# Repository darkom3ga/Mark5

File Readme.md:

<br />
<div align="center">
  
  <h3 align="center">Kratos Mark 5 </h3>
</div>

<details>
  <summary>Table of Contents</summary>
  <ol>
    <a href="#automating-the-running-of-the-rover">Automating the Working of the Rover</a>
    <a href="#bashrc-setup">Bashrc Setup</a>
  </ol>
</details>

## Getting Started

This repo is for easy of run of the Kratos rover and make it more organised .

## Automating the Working of the Rover

1. Install the required packages
    ```sh
    sudo apt install terminator xdotool sshpass
    ```
2. Git clone the repository and place the file named "kratos" in the ~/ directory ( home directory )</br>OR</br>Just Run the code 
    ```sh
    wget -P ~/ https://raw.githubusercontent.com/darkom3ga/Mark5/refs/heads/main/kratos
    ```

3. Run the command 
    ```sh
    chmod +x ~/kratos
    ```

4. Now run the kratos file from any terminal. 
    ```sh
    ~/kratos
    ```
    Type the Option and then hit Enter . Dont interefere / click while the automation is going one . It usually takes few second if the connections are ok .

## Bashrc Setup 

### In BaseStation

  ```sh
    export ROS_MASTER_URI=http://192.168.1.12:11311
    export ROS_IP=192.168.1.11
  ```

<p align="right">(<a href="#readme-top">back to top</a>)</p>

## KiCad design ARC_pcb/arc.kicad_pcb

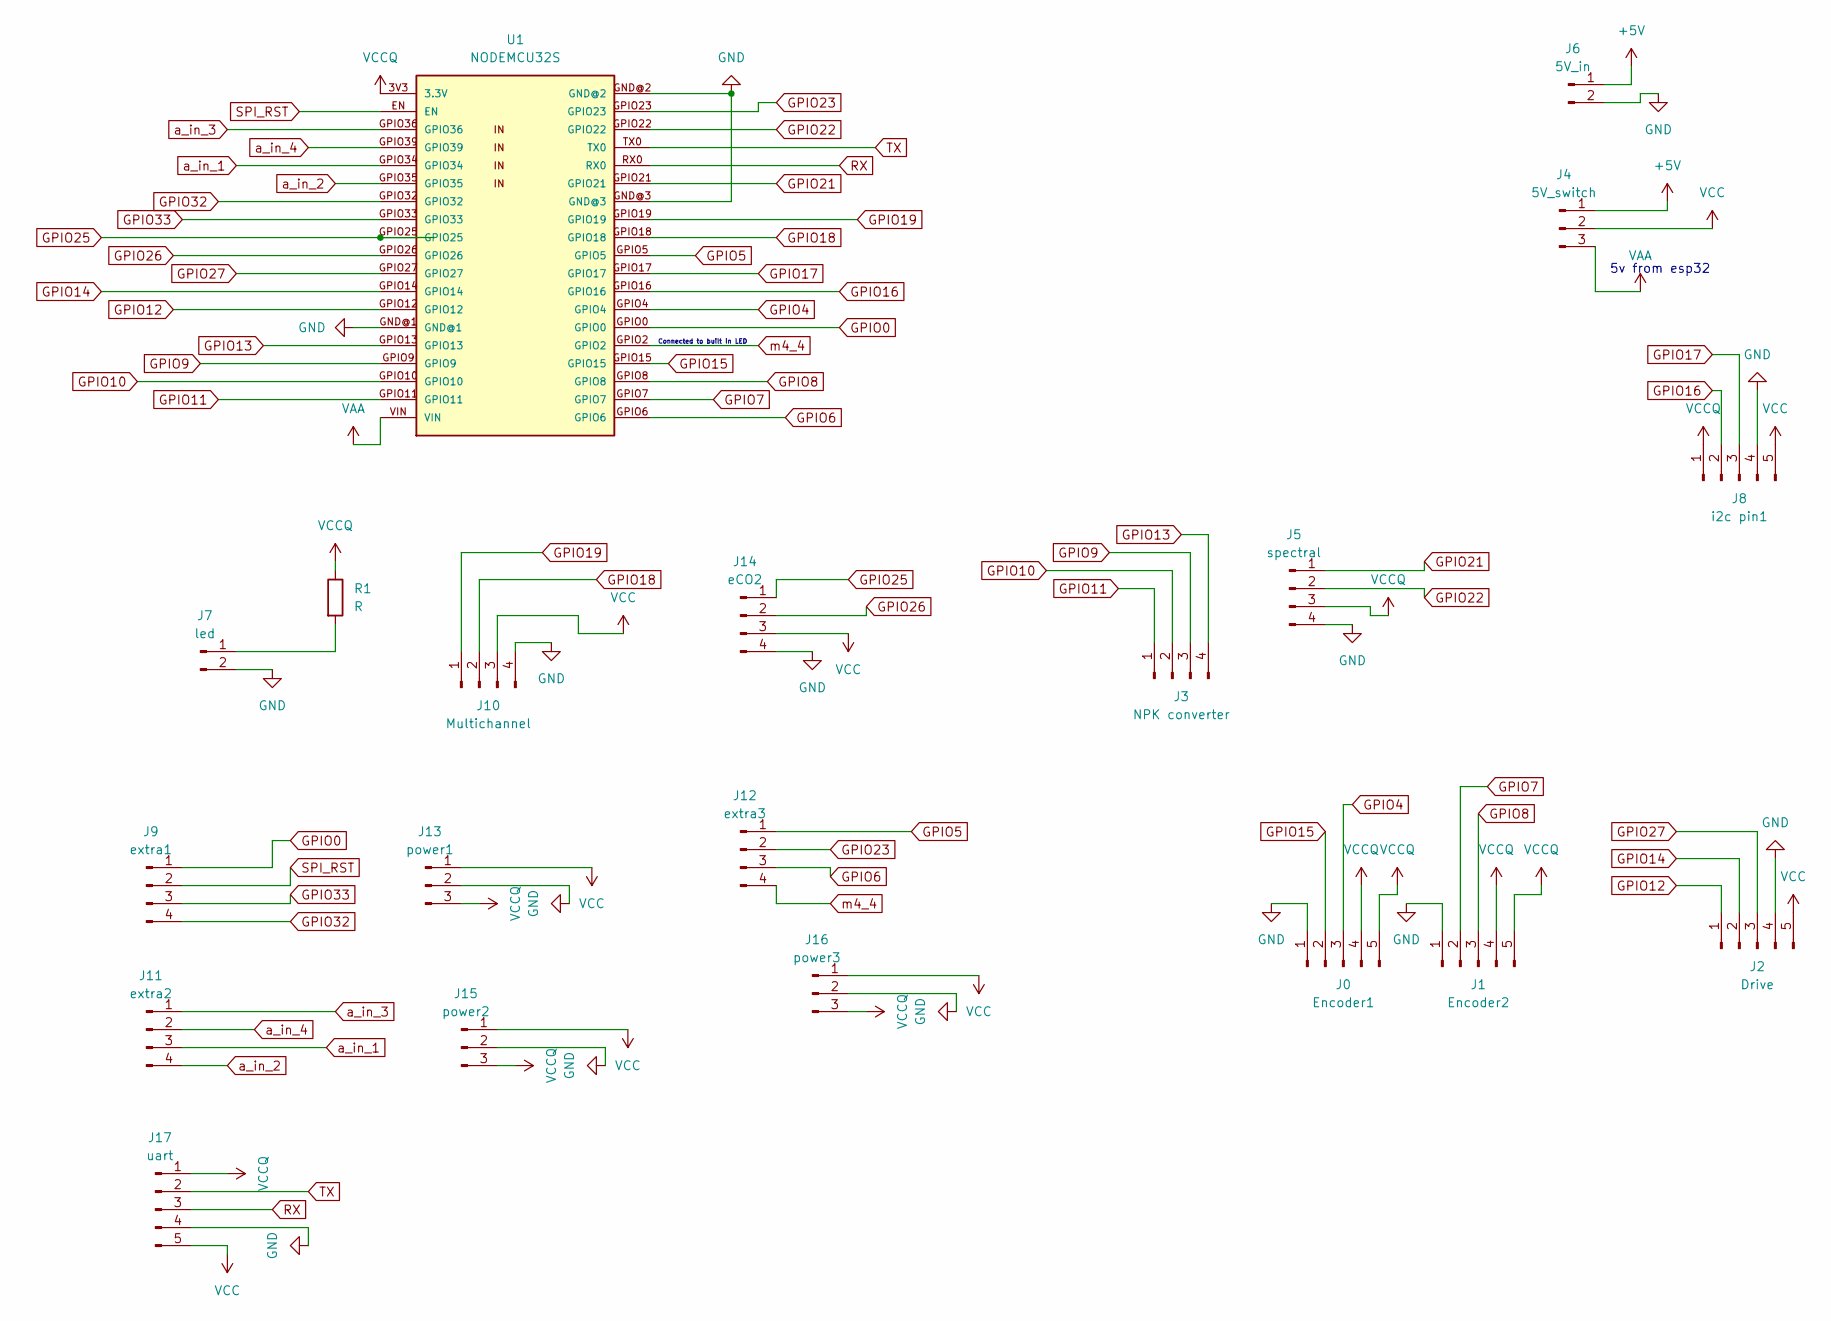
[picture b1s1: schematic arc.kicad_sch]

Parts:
J0: Encoder1; JST_XH_B5B-XH-A_1x05_P2.50mm_Vertical
J1: Encoder2; JST_XH_B5B-XH-A_1x05_P2.50mm_Vertical
J2: Drive; JST_XH_B5B-XH-A_1x05_P2.50mm_Vertical
J3: NPK converter; JST_XH_B4B-XH-A_1x04_P2.50mm_Vertical
J4: 5V_switch; JST_XH_B3B-XH-A_1x03_P2.50mm_Vertical
J5: spectral; JST_XH_B4B-XH-A_1x04_P2.50mm_Vertical
J6: 5V_in; JST_XH_B2B-XH-A_1x02_P2.50mm_Vertical
J7: led; JST_XH_B2B-XH-A_1x02_P2.50mm_Vertical
J8: i2c pin1; JST_XH_B5B-XH-A_1x05_P2.50mm_Vertical
J9: extra1; JST_XH_B4B-XH-A_1x04_P2.50mm_Vertical
J10: Multichannel; JST_XH_B4B-XH-A_1x04_P2.50mm_Vertical
J11: extra2; JST_XH_B4B-XH-A_1x04_P2.50mm_Vertical
J12: extra3; JST_XH_B4B-XH-A_1x04_P2.50mm_Vertical
J13: power1; JST_XH_B3B-XH-A_1x03_P2.50mm_Vertical
J14: eCO2; JST_XH_B4B-XH-A_1x04_P2.50mm_Vertical
J15: power2; JST_XH_B3B-XH-A_1x03_P2.50mm_Vertical
J16: power3; JST_XH_B3B-XH-A_1x03_P2.50mm_Vertical
J17: uart; JST_XH_B5B-XH-A_1x05_P2.50mm_Vertical
R1: R; R_Axial_DIN0207_L6.3mm_D2.5mm_P10.16mm_Horizontal
U1: NODEMCU32S; esp32_2in1_3dfixed

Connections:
+5V: J4.1, J6.1
GND: J0.1, J1.1, J2.4, J5.4, J6.2, J7.2, J8.4, J10.4, J13.2, J14.4, J15.2, J16.2, J17.4, U1.GND@1, U1.GND@2, U1.GND@3
GPIO0: J9.1, U1.GPIO0
GPIO4: J0.3, U1.GPIO4
GPIO5: J12.1, U1.GPIO5
GPIO6: J12.3, U1.GPIO6
GPIO7: J1.2, U1.GPIO7
GPIO8: J1.3, U1.GPIO8
GPIO9: J3.3, U1.GPIO9
GPIO10: J3.2, U1.GPIO10
GPIO11: J3.1, U1.GPIO11
GPIO12: J2.1, U1.GPIO12
GPIO13: J3.4, U1.GPIO13
GPIO14: J2.2, U1.GPIO14
GPIO15: J0.2, U1.GPIO15
GPIO16: J8.2, U1.GPIO16
GPIO17: J8.3, U1.GPIO17
GPIO18: J10.2, U1.GPIO18
GPIO19: J10.1, U1.GPIO19
GPIO21: J5.1, U1.GPIO21
GPIO22: J5.2, U1.GPIO22
GPIO23: J12.2, U1.GPIO23
GPIO25: J14.1, U1.GPIO25
GPIO26: J14.2, U1.GPIO26
GPIO27: J2.3, U1.GPIO27
GPIO32: J9.4, U1.GPIO32
GPIO33: J9.3, U1.GPIO33
unnamed: J7.1, R1.2
RX: J17.3, U1.RX0
SPI_RST: J9.2, U1.EN
TX: J17.2, U1.TX0
VAA: J4.3, U1.VIN
VCC: J2.5, J4.2, J8.5, J10.3, J13.1, J14.3, J15.1, J16.1, J17.5
VCCQ: J0.4, J0.5, J1.4, J1.5, J5.3, J8.1, J13.3, J15.3, J16.3, J17.1, R1.1, U1.3V3 (3.3V)
a_in_1: J11.3, U1.GPIO34
a_in_2: J11.4, U1.GPIO35
a_in_3: J11.1, U1.GPIO36
a_in_4: J11.2, U1.GPIO39
m4_4: J12.4, U1.GPIO2

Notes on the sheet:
Connected to built in LED
5v from esp32

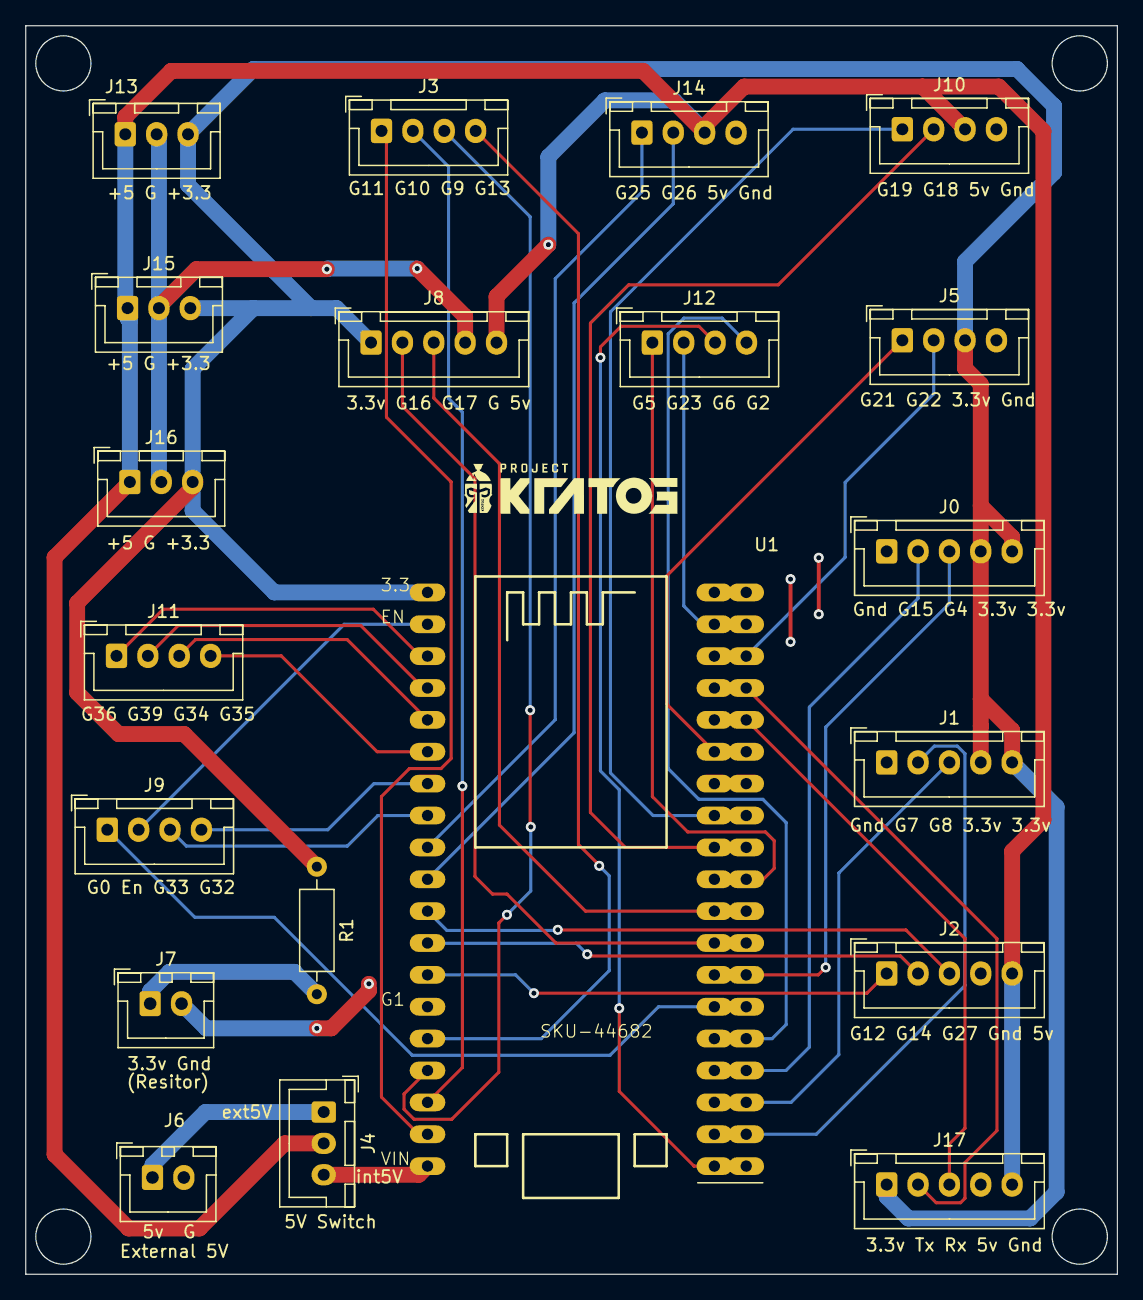
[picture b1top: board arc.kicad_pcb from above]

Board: 2 copper layers, 87.0 x 99.5 mm, 21 parts (0 on the bottom side), 39 nets.

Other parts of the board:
KratosLogo: LOGO; KratosLOGO

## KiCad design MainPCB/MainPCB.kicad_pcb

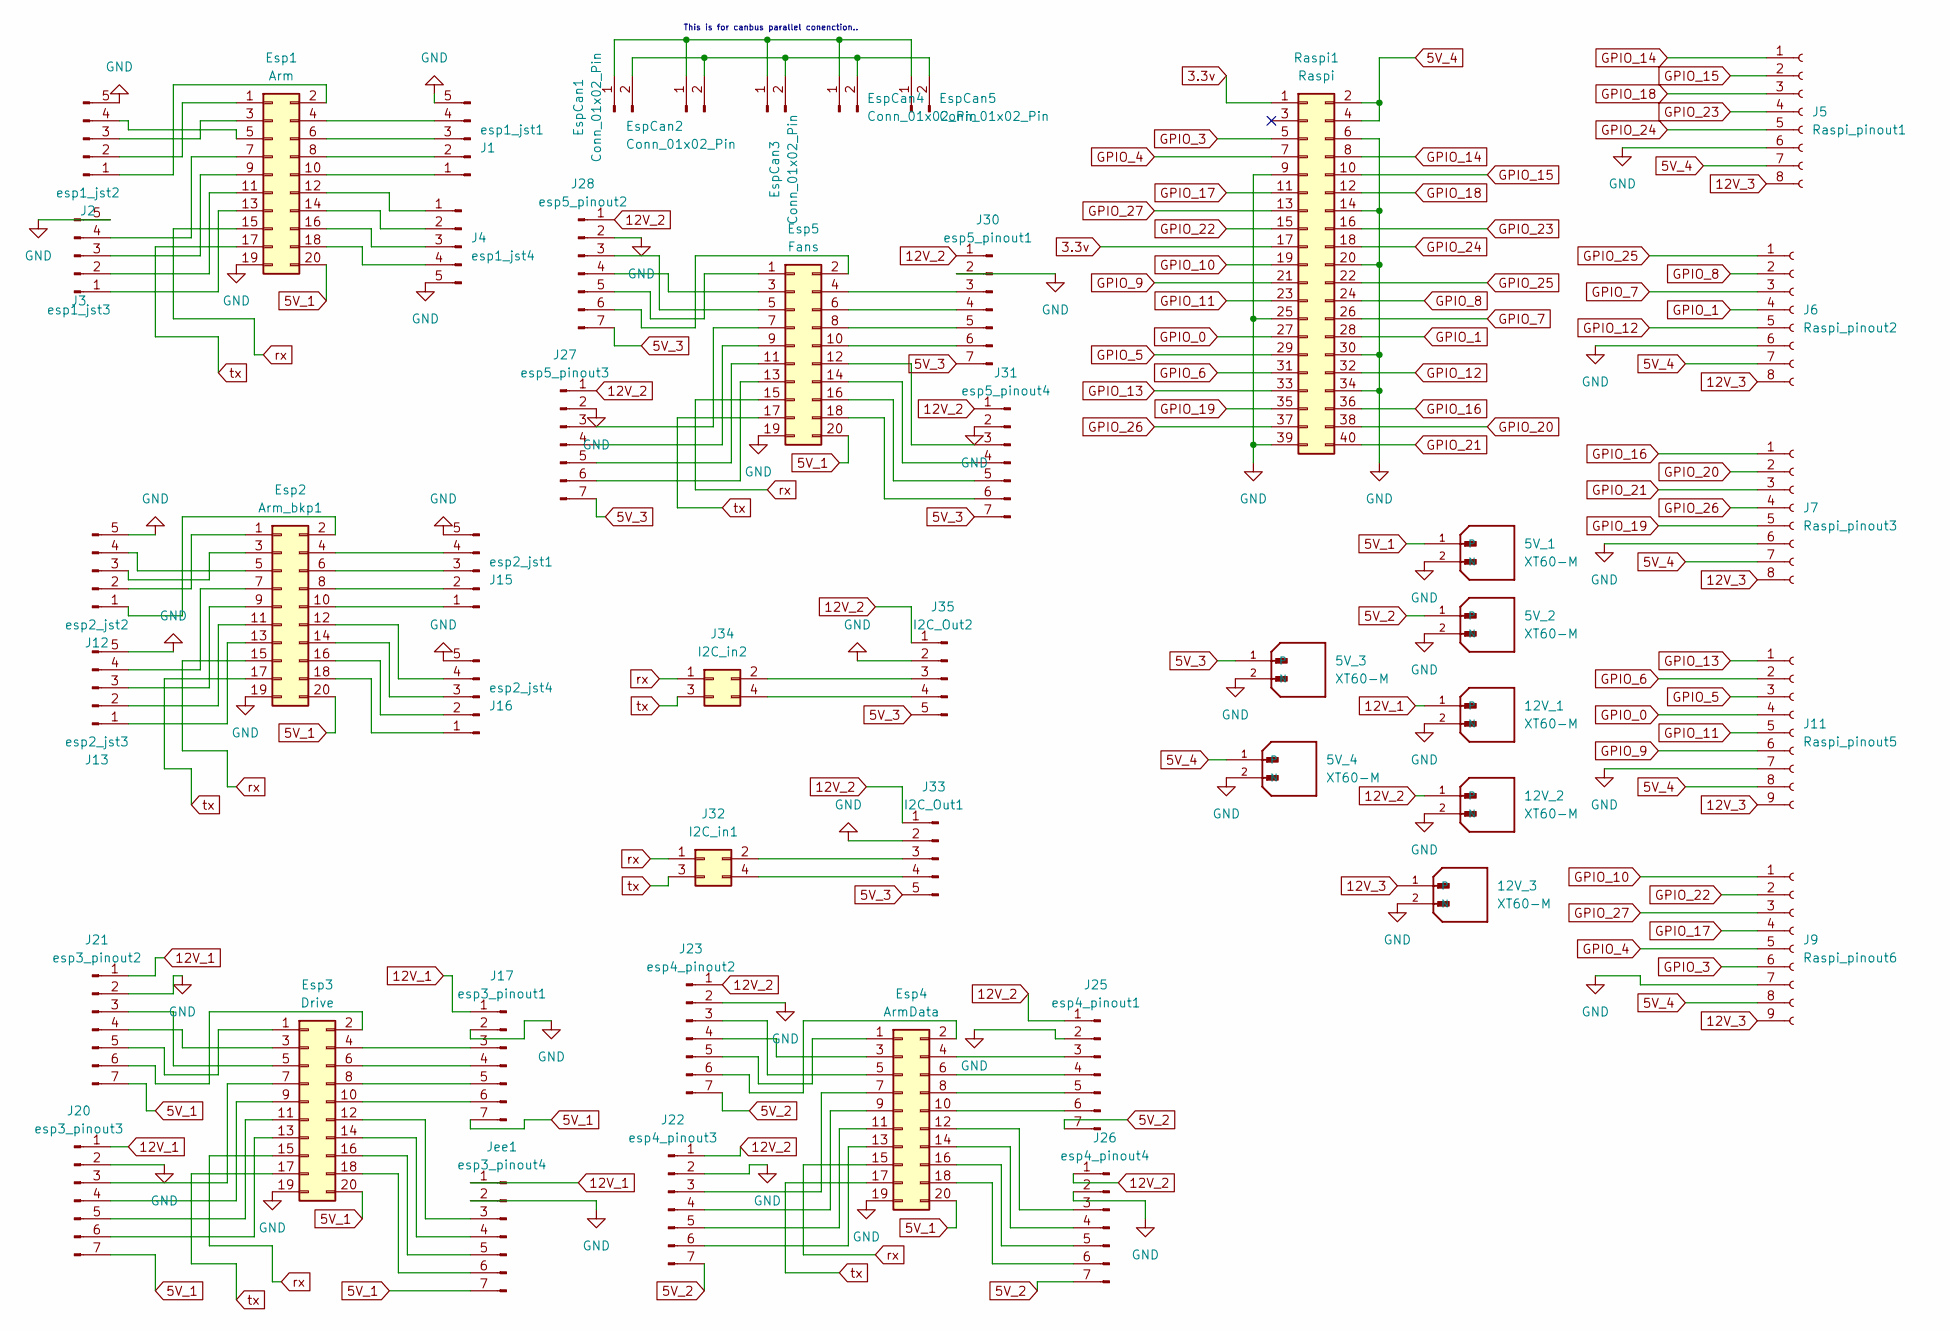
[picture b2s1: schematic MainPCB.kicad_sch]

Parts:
5V_1, 5V_2, 5V_3, 5V_4, 12V_1, 12V_2, 12V_3: XT60-M; AMASS_XT60-M_1x02_P7.20mm_Vertical; PARTREV V1.2
Esp1: Arm; PinSocket_2x10_P2.54mm_Vertical
Esp2: Arm_bkp1; PinSocket_2x10_P2.54mm_Vertical
Esp3: Drive; PinSocket_2x10_P2.54mm_Vertical
Esp4: ArmData; PinSocket_2x10_P2.54mm_Vertical
Esp5: Fans; PinSocket_2x10_P2.54mm_Vertical
EspCan1, EspCan2, EspCan3, EspCan4, EspCan5: Conn_01x02_Pin; PinHeader_1x02_P2.54mm_Vertical
J1: esp1_jst1; JST_XH_S5B-XH-A_1x05_P2.50mm_Horizontal
J2: esp1_jst2; JST_XH_S5B-XH-A_1x05_P2.50mm_Horizontal
J3: esp1_jst3; JST_XH_S5B-XH-A_1x05_P2.50mm_Horizontal
J4: esp1_jst4; JST_XH_S5B-XH-A_1x05_P2.50mm_Horizontal
J5: Raspi_pinout1; PinHeader_1x08_P2.54mm_Vertical
J6: Raspi_pinout2; PinHeader_1x08_P2.54mm_Vertical
J7: Raspi_pinout3; PinHeader_1x08_P2.54mm_Vertical
J9: Raspi_pinout6; PinHeader_1x09_P2.54mm_Vertical
J11: Raspi_pinout5; PinHeader_1x09_P2.54mm_Vertical
J12: esp2_jst2; JST_XH_S5B-XH-A_1x05_P2.50mm_Horizontal
J13: esp2_jst3; JST_XH_S5B-XH-A_1x05_P2.50mm_Horizontal
J15: esp2_jst1; JST_XH_S5B-XH-A_1x05_P2.50mm_Horizontal
J16: esp2_jst4; JST_XH_S5B-XH-A_1x05_P2.50mm_Horizontal
J17: esp3_pinout1; PinHeader_1x07_P2.54mm_Vertical
J20: esp3_pinout3; PinHeader_1x07_P2.54mm_Vertical
J21: esp3_pinout2; PinHeader_1x07_P2.54mm_Vertical
J22: esp4_pinout3; PinHeader_1x07_P2.54mm_Vertical
J23: esp4_pinout2; PinHeader_1x07_P2.54mm_Vertical
J25: esp4_pinout1; PinHeader_1x07_P2.54mm_Vertical
J26: esp4_pinout4; PinHeader_1x07_P2.54mm_Vertical
J27: esp5_pinout3; PinHeader_1x07_P2.54mm_Vertical
J28: esp5_pinout2; PinHeader_1x07_P2.54mm_Vertical
J30: esp5_pinout1; PinHeader_1x07_P2.54mm_Vertical
J31: esp5_pinout4; PinHeader_1x07_P2.54mm_Vertical
J32: I2C_in1; PinHeader_2x02_P2.54mm_Vertical
J33: I2C_Out1; PinHeader_1x05_P2.54mm_Vertical
J34: I2C_in2; PinHeader_2x02_P2.54mm_Vertical
J35: I2C_Out2; PinHeader_1x05_P2.54mm_Vertical
Jee1: esp3_pinout4; PinHeader_1x07_P2.54mm_Vertical
Raspi1: Raspi; PinSocket_2x20_P2.54mm_Horizontal

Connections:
3.3v: Raspi1.1, Raspi1.17
5V_1: 5V_1.1, Esp1.20, Esp2.20, Esp3.20, Esp4.20, Esp5.20, J17.7, J20.7, J21.7, Jee1.7
5V_2: 5V_2.1, J22.7, J23.7, J25.7, J26.7
5V_3: 5V_3.1, J27.7, J28.7, J30.7, J31.7, J33.5, J35.5
5V_4: 5V_4.1, J5.7, J6.7, J7.7, J9.8, J11.8, Raspi1.2, Raspi1.4
12V_1: 12V_1.1, J17.1, J20.1, J21.1, Jee1.1
12V_2: 12V_2.1, J22.1, J23.1, J25.1, J26.1, J27.1, J28.1, J30.1, J31.1, J33.1, J35.1
12V_3: 12V_3.1, J5.8, J6.8, J7.8, J9.9, J11.9
GND: 5V_1.2 (N), 5V_2.2 (N), 5V_3.2 (N), 5V_4.2 (N), 12V_1.2 (N), 12V_2.2 (N), 12V_3.2 (N), Esp1.19, Esp2.19, Esp3.19, Esp4.19, Esp5.19, J1.5, J2.5, J3.5, J4.5, J5.6, J6.6, J7.6, J9.7, J11.7, J12.5, J13.5, J15.5, J16.5, J17.2, J20.2, J21.2, J22.2, J23.2, J25.2, J26.2, J27.2, J28.2, J30.2, J31.2, J33.2, J35.2, Jee1.2, Raspi1.6, Raspi1.9, Raspi1.14, Raspi1.20, Raspi1.25, Raspi1.30, Raspi1.34, Raspi1.39
GPIO_0: J11.4, Raspi1.27
GPIO_1: J6.4, Raspi1.28
GPIO_3: J9.6, Raspi1.5
GPIO_4: J9.5, Raspi1.7
GPIO_5: J11.3, Raspi1.29
GPIO_6: J11.2, Raspi1.31
GPIO_7: J6.3, Raspi1.26
GPIO_8: J6.2, Raspi1.24
GPIO_9: J11.6, Raspi1.21
GPIO_10: J9.1, Raspi1.19
GPIO_11: J11.5, Raspi1.23
GPIO_12: J6.5, Raspi1.32
GPIO_13: J11.1, Raspi1.33
GPIO_14: J5.1, Raspi1.8
GPIO_15: J5.2, Raspi1.10
GPIO_16: J7.1, Raspi1.36
GPIO_17: J9.4, Raspi1.11
GPIO_18: J5.3, Raspi1.12
GPIO_19: J7.5, Raspi1.35
GPIO_20: J7.2, Raspi1.38
GPIO_21: J7.3, Raspi1.40
GPIO_22: J9.2, Raspi1.15
GPIO_23: J5.4, Raspi1.16
GPIO_24: J5.5, Raspi1.18
GPIO_25: J6.1, Raspi1.22
GPIO_26: J7.4, Raspi1.37
GPIO_27: J9.3, Raspi1.13
unnamed: Esp1.1, J2.2
unnamed: Esp1.2, J2.1
unnamed: Esp1.3, J2.3
unnamed: Esp1.4, J1.4
unnamed: Esp1.5, J2.4
unnamed: Esp1.6, J1.3
unnamed: Esp1.7, J3.4
unnamed: Esp1.8, J1.2
unnamed: Esp1.9, J3.3
unnamed: Esp1.10, J1.1
unnamed: Esp1.11, J3.2
unnamed: Esp1.12, J4.1
unnamed: Esp1.13, J3.1
unnamed: Esp1.14, J4.2
unnamed: Esp1.16, J4.3
unnamed: Esp1.18, J4.4
unnamed: Esp2.1, J12.2
unnamed: Esp2.2, J12.1
unnamed: Esp2.3, J12.3
unnamed: Esp2.4, J15.4
unnamed: Esp2.5, J12.4
unnamed: Esp2.6, J15.3
unnamed: Esp2.7, J13.4
unnamed: Esp2.8, J15.2
unnamed: Esp2.9, J13.3
unnamed: Esp2.10, J15.1
unnamed: Esp2.11, J13.2
unnamed: Esp2.12, J16.4
unnamed: Esp2.13, J13.1
unnamed: Esp2.14, J16.3
unnamed: Esp2.16, J16.2
unnamed: Esp2.18, J16.1
unnamed: Esp3.1, J21.5
unnamed: Esp3.2, J21.6
unnamed: Esp3.3, J21.4
unnamed: Esp3.4, J17.3
unnamed: Esp3.5, J21.3
unnamed: Esp3.6, J17.4
unnamed: Esp3.7, J20.3
unnamed: Esp3.8, J17.5
unnamed: Esp3.9, J20.4
unnamed: Esp3.10, J17.6
unnamed: Esp3.11, J20.5
unnamed: Esp3.12, Jee1.3
unnamed: Esp3.13, J20.6
unnamed: Esp3.14, Jee1.4
unnamed: Esp3.16, Jee1.5
unnamed: Esp3.18, Jee1.6
unnamed: Esp4.1, J23.5
unnamed: Esp4.2, J23.6
unnamed: Esp4.3, J23.4
unnamed: Esp4.4, J25.3
unnamed: Esp4.5, J23.3
unnamed: Esp4.6, J25.4
unnamed: Esp4.7, J22.3
unnamed: Esp4.8, J25.5
unnamed: Esp4.9, J22.4
unnamed: Esp4.10, J25.6
unnamed: Esp4.11, J22.5
unnamed: Esp4.12, J26.3
unnamed: Esp4.13, J22.6
unnamed: Esp4.14, J26.4
unnamed: Esp4.16, J26.5
unnamed: Esp4.18, J26.6
unnamed: Esp5.1, J28.5
unnamed: Esp5.2, J28.6
unnamed: Esp5.3, J28.4
unnamed: Esp5.4, J30.3
unnamed: Esp5.5, J28.3
unnamed: Esp5.6, J30.4
unnamed: Esp5.7, J27.3
unnamed: Esp5.8, J30.5
unnamed: Esp5.9, J27.4
unnamed: Esp5.10, J30.6
unnamed: Esp5.11, J27.5
unnamed: Esp5.12, J31.3
unnamed: Esp5.13, J27.6
unnamed: Esp5.14, J31.4
unnamed: Esp5.16, J31.5
unnamed: Esp5.18, J31.6
unnamed: EspCan1.1, EspCan2.1, EspCan3.1, EspCan4.1, EspCan5.1
unnamed: EspCan1.2, EspCan2.2, EspCan3.2, EspCan4.2, EspCan5.2
unnamed: J32.2, J33.3
unnamed: J32.4, J33.4
unnamed: J34.2, J35.3
unnamed: J34.4, J35.4
rx: Esp1.15, Esp2.15, Esp3.15, Esp4.15, Esp5.15, J32.1, J34.1
tx: Esp1.17, Esp2.17, Esp3.17, Esp4.17, Esp5.17, J32.3, J34.3

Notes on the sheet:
This is for canbus parallel conenction..

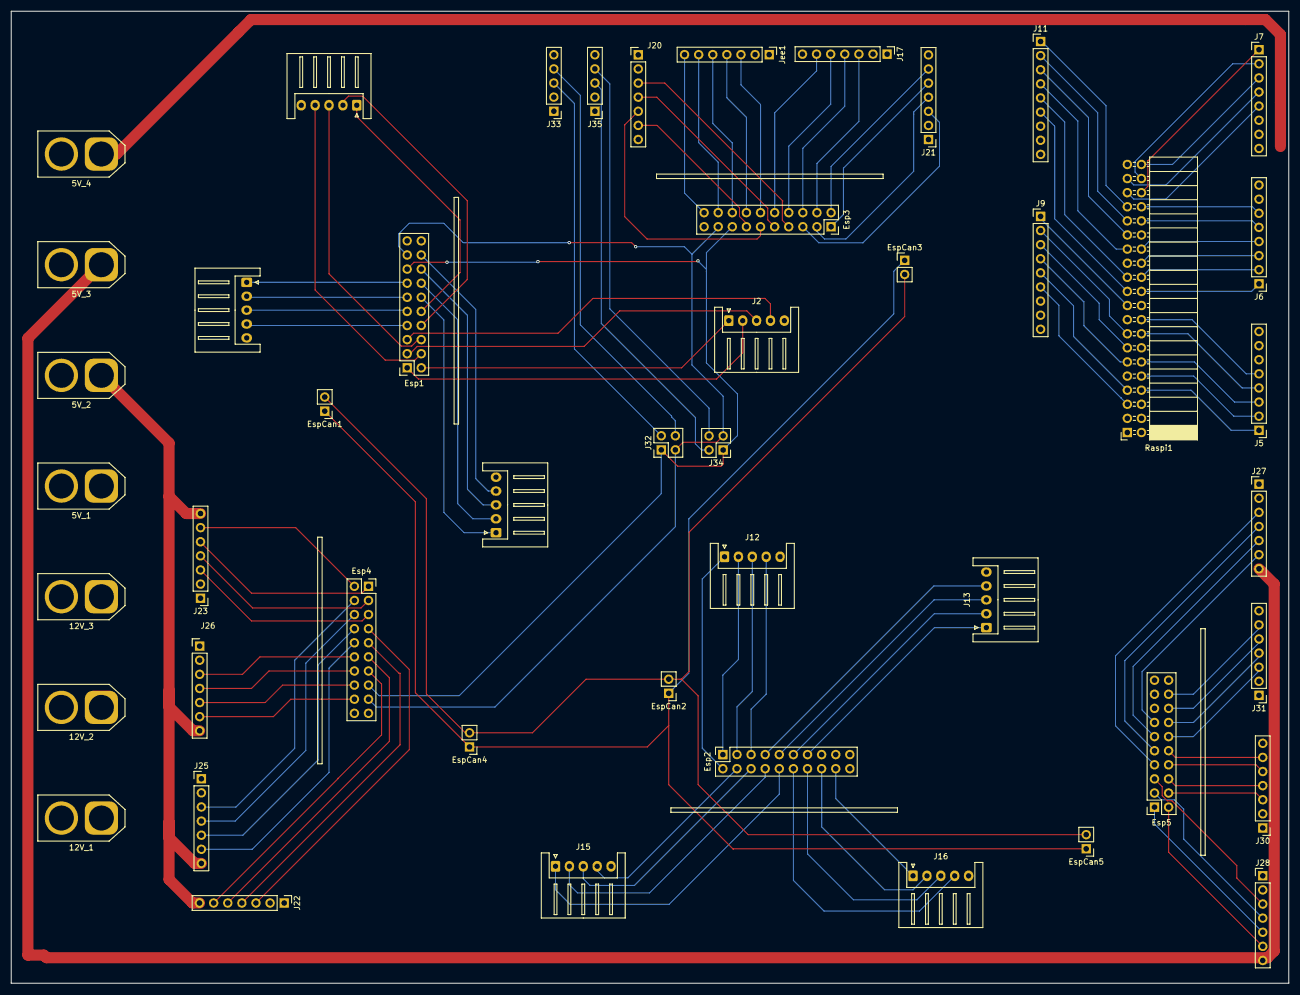
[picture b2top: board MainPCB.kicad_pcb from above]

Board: 2 copper layers, 230.0 x 175.0 mm, 47 parts (0 on the bottom side), 124 nets.

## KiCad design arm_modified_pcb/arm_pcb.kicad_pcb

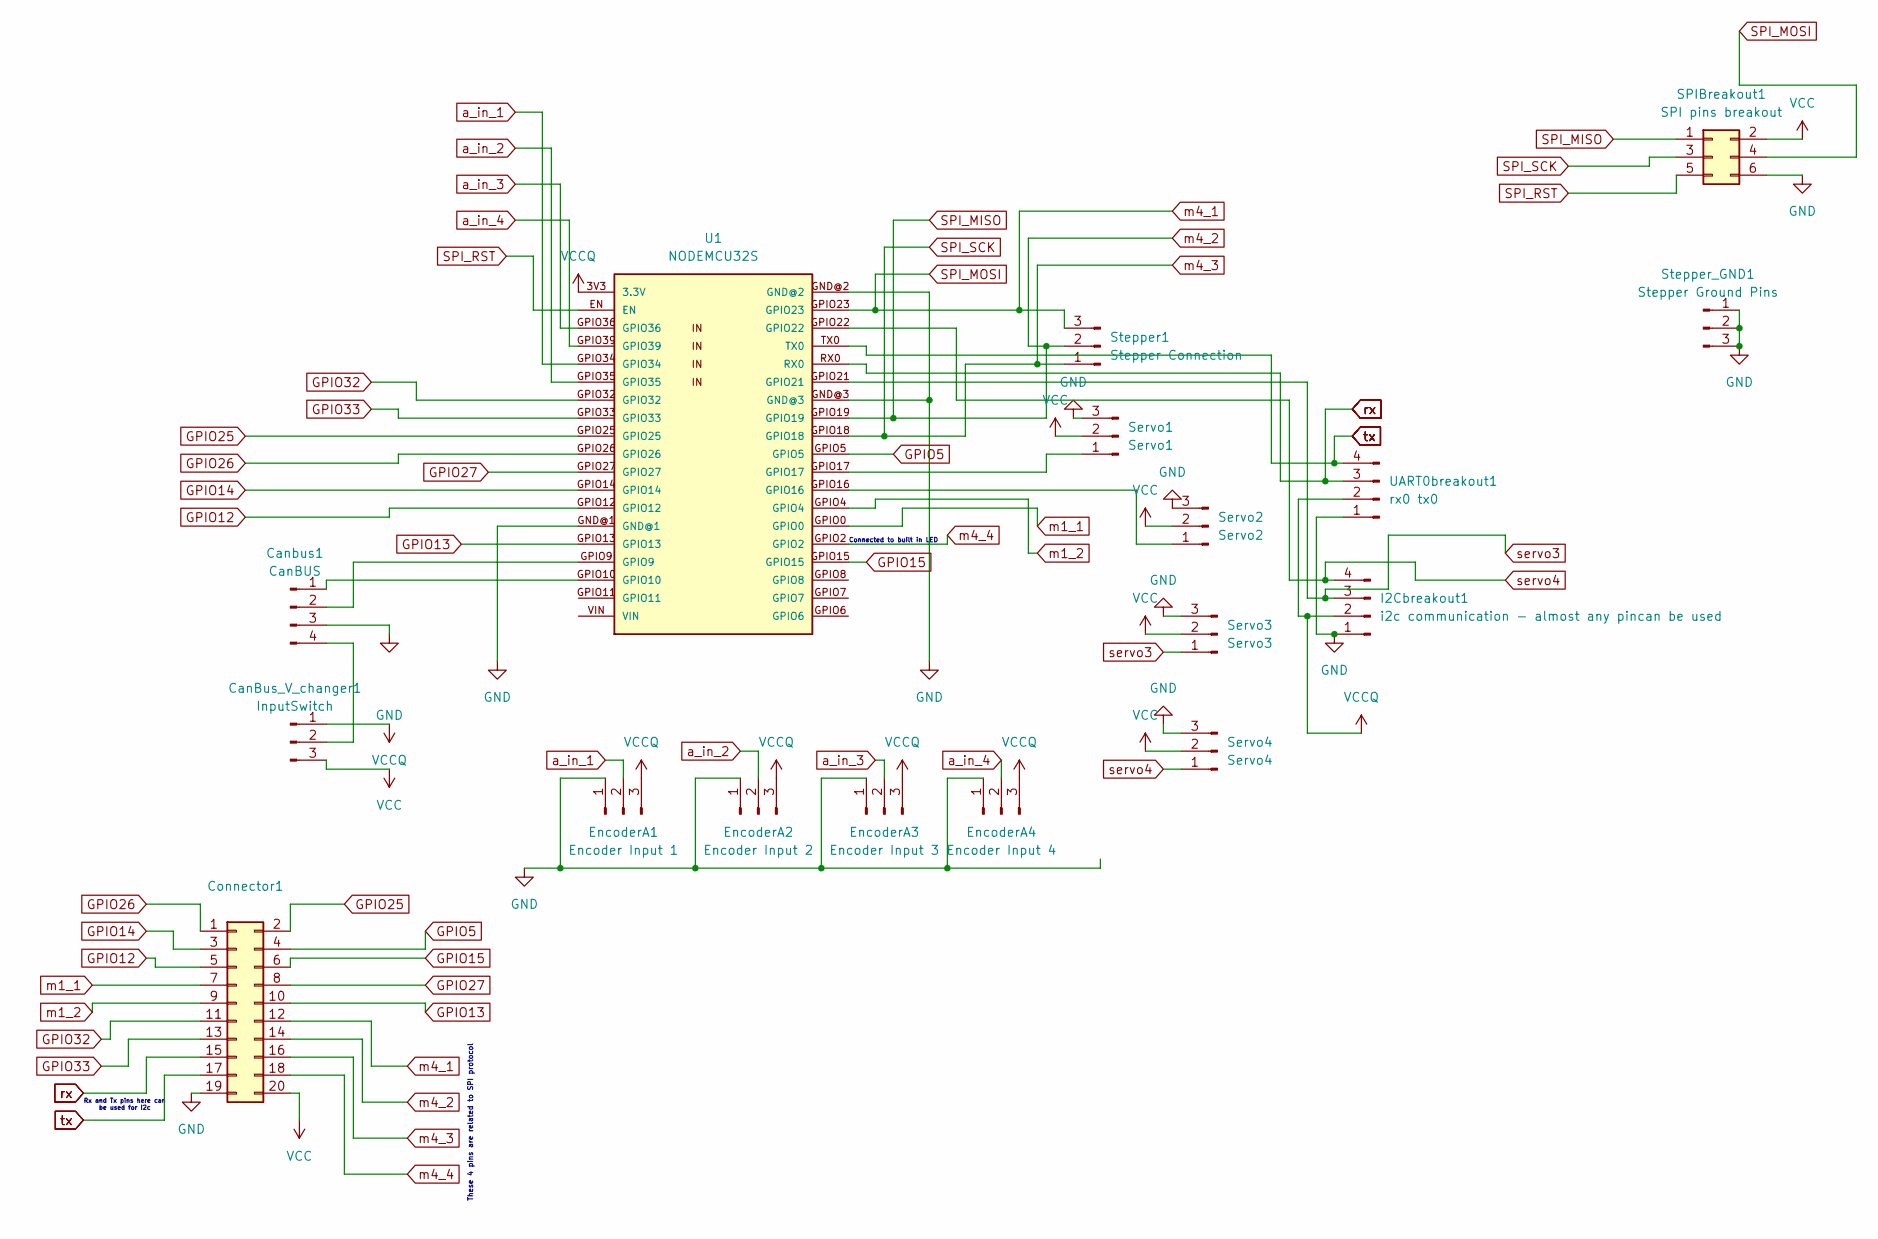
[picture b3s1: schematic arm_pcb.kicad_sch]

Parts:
CanBus_V_changer1: InputSwitch; PinHeader_1x03_P2.54mm_Vertical
Canbus1: CanBUS; PinSocket_1x04_P2.54mm_Horizontal
Connector1: Connector; PinHeader_2x10_P2.54mm_Horizontal
EncoderA1: Encoder Input 1; JST_XH_B3B-XH-A_1x03_P2.50mm_Vertical
EncoderA2: Encoder Input 2; JST_XH_B3B-XH-A_1x03_P2.50mm_Vertical
EncoderA3: Encoder Input 3; JST_XH_B3B-XH-A_1x03_P2.50mm_Vertical
EncoderA4: Encoder Input 4; JST_XH_B3B-XH-A_1x03_P2.50mm_Vertical
I2Cbreakout1: i2c communication - almost any pincan be used; JST_XH_B4B-XH-A_1x04_P2.50mm_Vertical
SPIBreakout1: SPI pins breakout; PinHeader_2x03_P2.54mm_Vertical
Servo1: Servo1; JST_XH_B3B-XH-A_1x03_P2.50mm_Vertical
Servo2: Servo2; JST_XH_B3B-XH-A_1x03_P2.50mm_Vertical
Servo3: Servo3; JST_XH_B3B-XH-A_1x03_P2.50mm_Vertical
Servo4: Servo4; JST_XH_B3B-XH-A_1x03_P2.50mm_Vertical
Stepper1: Stepper Connection; JST_XH_B3B-XH-A_1x03_P2.50mm_Vertical
Stepper_GND1: Stepper Ground Pins; JST_XH_B3B-XH-A_1x03_P2.50mm_Vertical
U1: NODEMCU32S
UART0breakout1: rx0 tx0; JST_XH_B4B-XH-A_1x04_P2.50mm_Vertical

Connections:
GND: Canbus1.3, Connector1.19, EncoderA1.1, EncoderA2.1, EncoderA3.1, EncoderA4.1, I2Cbreakout1.1, SPIBreakout1.6, Servo1.3, Servo2.3, Servo3.3, Servo4.3, Stepper_GND1.1, Stepper_GND1.2, Stepper_GND1.3, U1.GND@1, U1.GND@2, U1.GND@3, UART0breakout1.1; also elsewhere on the board
GPIO5: Connector1.4, U1.GPIO5
GPIO12: Connector1.5, U1.GPIO12
GPIO13: Connector1.10, U1.GPIO13
GPIO14: Connector1.3, U1.GPIO14
GPIO15: Connector1.6, U1.GPIO15
GPIO25: Connector1.2, U1.GPIO25
GPIO26: Connector1.1, U1.GPIO26
GPIO27: Connector1.8, U1.GPIO27
GPIO32: Connector1.11, U1.GPIO32
GPIO33: Connector1.13, U1.GPIO33
unnamed: CanBus_V_changer1.2, Canbus1.4
unnamed: Canbus1.1, U1.GPIO10
unnamed: Canbus1.2, U1.GPIO9
unnamed: Servo1.1, U1.GPIO17
unnamed: Servo2.1, U1.GPIO16
SPI_MISO: Connector1.14, SPIBreakout1.1, Stepper1.2, U1.GPIO19
SPI_MOSI: Connector1.12, SPIBreakout1.4, Stepper1.3, U1.GPIO23
SPI_RST: SPIBreakout1.5, U1.EN
SPI_SCK: Connector1.16, SPIBreakout1.3, Stepper1.1, U1.GPIO18
VCC: CanBus_V_changer1.3, Connector1.20, SPIBreakout1.2, Servo1.2, Servo2.2, Servo3.2, Servo4.2; also elsewhere on the board
VCCQ: CanBus_V_changer1.1, EncoderA1.3, EncoderA2.3, EncoderA3.3, EncoderA4.3, I2Cbreakout1.2, U1.3V3 (3.3V), UART0breakout1.2; also elsewhere on the board
a_in_1: EncoderA1.2, U1.GPIO34
a_in_2: EncoderA2.2, U1.GPIO35
a_in_3: EncoderA3.2, U1.GPIO36
a_in_4: EncoderA4.2, U1.GPIO39
m1_1: Connector1.7, U1.GPIO0
m1_2: Connector1.9, U1.GPIO4
m4_4: Connector1.18, U1.GPIO2
rx: Connector1.15, U1.RX0, UART0breakout1.3
servo3: I2Cbreakout1.3, Servo3.1, U1.GPIO21
servo4: I2Cbreakout1.4, Servo4.1, U1.GPIO22
tx: Connector1.17, U1.TX0, UART0breakout1.4

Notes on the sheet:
Connected to built in LED
Rx and Tx pins here can be used for i2c
These 4 pins are related to SPI protocol

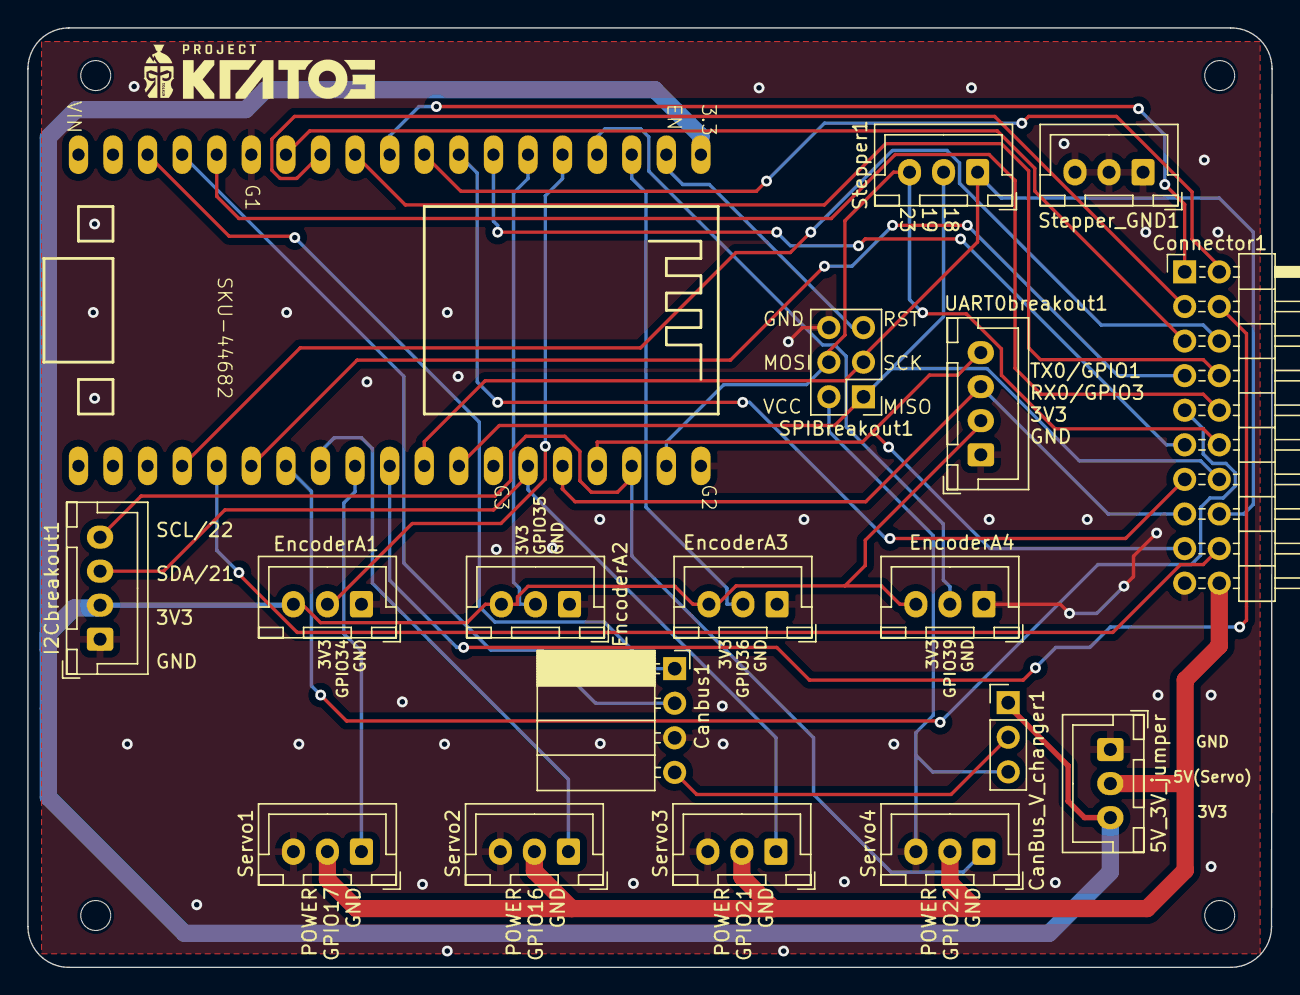
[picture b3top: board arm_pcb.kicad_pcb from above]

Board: 2 copper layers, 91.4 x 69.0 mm, 23 parts (0 on the bottom side), 33 nets.

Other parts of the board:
5V_3V_jumper: JST_XH_B3B-XH-A_1x03_P2.50mm_Vertical
KratosLogo: LOGO
mountinghole1, mountinghole2, mountinghole3, mountinghole4: MountingHole_2.2mm_M2

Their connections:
GND: 5V_3V_jumper.1; also elsewhere on the board
VCC: 5V_3V_jumper.2; also elsewhere on the board
VCCQ: 5V_3V_jumper.3; also elsewhere on the board

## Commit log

2024-11-27 Simple automation
2024-12-09 Arm/LD PCB : Old PCB modified
2024-12-09 Arm/Ld Modified
2024-12-09 Arm/LD PCB modified
2024-12-09 Fix Readme.md
2024-12-13 Few Small Changes
2024-12-13 Few File Changes
2024-12-13 MainPCB : Not Complete ( Basic Schematic Ready )
2025-01-13 camera
2025-01-18 camera : cleanup implemented
2025-01-19 it was hard to do this camera
2025-01-27 test only version temp cameras
2025-04-21 Arc PCB
